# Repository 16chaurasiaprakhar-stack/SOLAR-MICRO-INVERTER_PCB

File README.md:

# HAR-SMI-500 — High-Altitude Resilient 500W Solar Micro-Inverter

A high-altitude, extreme-environment **500W solar micro-inverter architecture** designed for operation under subzero temperatures and reduced atmospheric pressure. The design combines a **GaN-based LLC DC-DC conversion stage**, isolated planar transformer, **SiC full-bridge grid inverter**, LCL filtering, deterministic C2000 control, and ESP32-S3-based edge telemetry.

The system is designed around a **28–50V DC PV input**, **400V DC-link**, and **230V AC / 50Hz grid output**, with a target peak efficiency of **97.2%**.

## Key Features

* **500W continuous power conversion**
* 28–50V DC photovoltaic input
* 400V regulated DC-link
* 230V AC, 50Hz single-phase output
* GaN full-bridge LLC converter
* 2:20 planar isolation transformer
* SiC full-bridge grid inverter
* LCL output filter
* TI **TMS320F28379D C2000** real-time power controller
* **ESP32-S3** edge-processing and telemetry controller
* Galvanically isolated SPI communication using **ISO7741-Q1**
* Incremental Conductance MPPT
* SOGI-PLL grid synchronization
* 20kHz proportional-resonant current control
* Hardware over-voltage and over-current trip protection
* PT100, BME280, SHT45 and solar-irradiance sensing
* SX1262-based LoRaWAN telemetry
* Autonomous cold-start pre-heating using a 25W PTC heater
* High-altitude PCB clearance and creepage design
* Designed for −40°C to +55°C operation

The complete architecture is divided into hierarchical functional blocks covering PV input protection, LLC conversion, isolation and rectification, DC-link storage, SiC inversion, LCL filtering, gate drivers, sensing, dual-MCU control, RF telemetry, auxiliary power, and mechanical interfaces.

## Control & Protection

The C2000 controller provides the deterministic power-conversion control loop, including MPPT, LLC frequency modulation, grid synchronization, PR current control, and hardware Trip-Zone protection. The ESP32-S3 is isolated from the power-control domain and handles environmental diagnostics, cold-start supervision, data logging, and wireless telemetry.

## High-Altitude Design

The architecture incorporates altitude-aware electrical insulation design with an enforced **≥4.5 mm clearance** and **≥6.0 mm creepage**, along with milled isolation slots, conformal coating, selective potting, and minimized high-dv/dt power loops.

## Cold-Start System  

At temperatures below −20°C, the system enters an autonomous pre-heating state before enabling normal inverter operation. A 25W PTC heater combined with controlled GaN switching provides approximately 38W of heating power, targeting a transition from −40°C to −10°C in approximately 11.58 minutes.

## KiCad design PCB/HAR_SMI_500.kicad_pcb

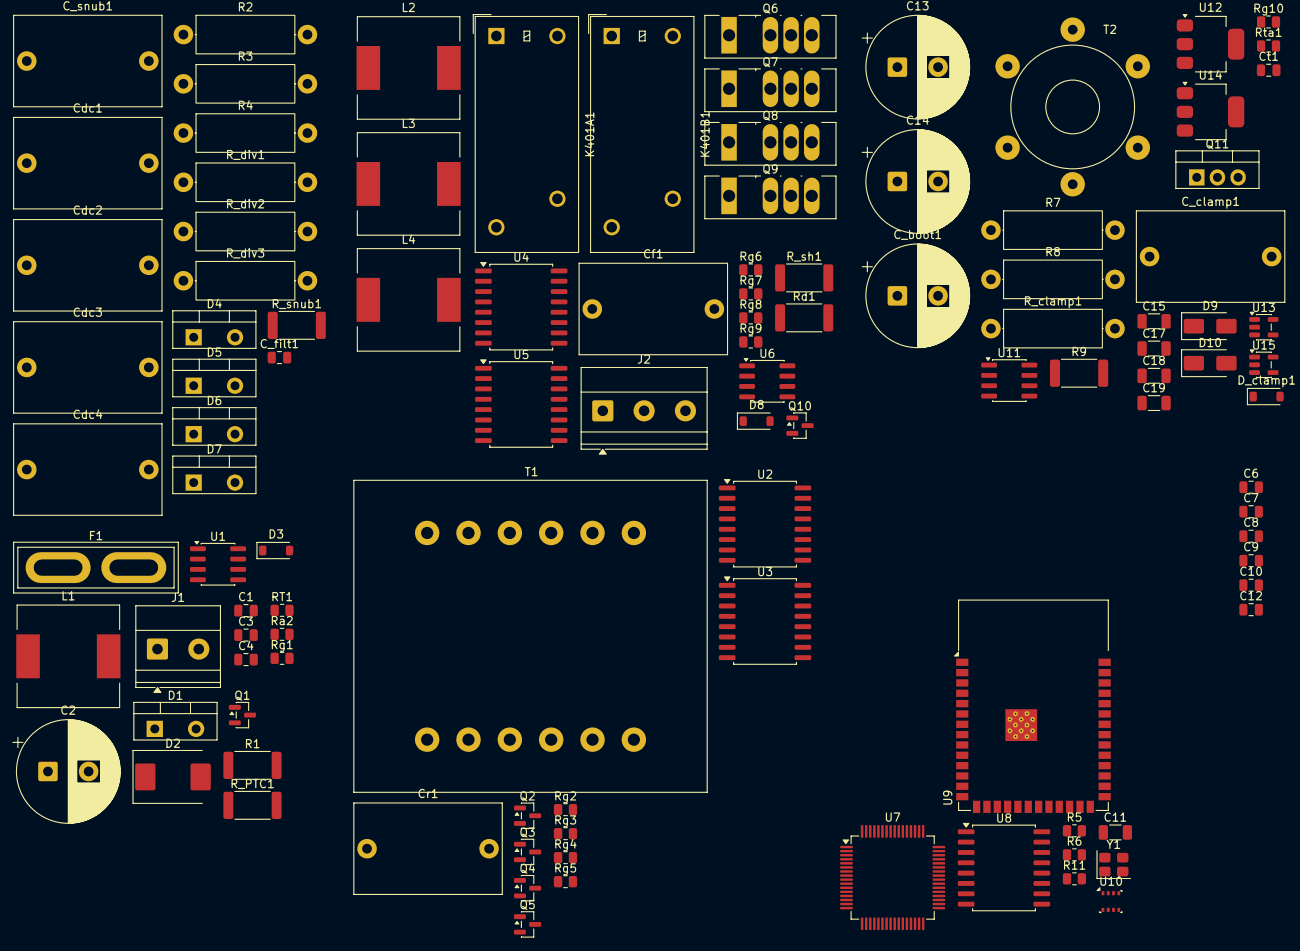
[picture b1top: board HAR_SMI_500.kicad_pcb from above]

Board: 2 copper layers, 108 parts (0 on the bottom side), 90 nets, no tracks yet.

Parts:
C1: 10uF 100V X7R MLCC; C_0805_2012Metric
C2: 470uF 100V Electrolytic; CP_Radial_D12.5mm_P5.00mm
C3: 100nF 50V Decouple; C_0805_2012Metric
C4: 100nF 50V RTD Filter; C_0805_2012Metric
C6, C8: 18pF 50V C0G; C_0805_2012Metric
C7: 2.2uF VDDC Decouple; C_0805_2012Metric
C9: 0.1uF 50V (Pri Vcc); C_0805_2012Metric
C10: 0.1uF 50V (Sec Vcc); C_0805_2012Metric
C11: 1uF EN Delay; C_1206_3216Metric
C12: 10uF 10V (ESP 3V3); C_0805_2012Metric
C13: 100uF 35V Low-ESR; CP_Radial_D12.5mm_P5.00mm
C14: 220uF 16V Low-ESR; CP_Radial_D12.5mm_P5.00mm
C15: 10uF 25V; C_1206_3216Metric
C17, C19: 10uF 10V; C_1206_3216Metric
C18: 10uF 16V; C_1206_3216Metric
C_boot1: 47uF 35V Low-ESR; CP_Radial_D12.5mm_P5.00mm
C_clamp1: 2.2nF 1kV; C_Rect_L18.0mm_W11.0mm_P15.00mm_FKS3_FKP3
C_filt1: 10nF 50V C0G ADC Filter; C_0805_2012Metric
C_snub1: 1nF 1kV Ceramic; C_Rect_L18.0mm_W11.0mm_P15.00mm_FKS3_FKP3
Cdc1, Cdc2, Cdc3, Cdc4: 47uF 450V Polypropylene; C_Rect_L18.0mm_W11.0mm_P15.00mm_FKS3_FKP3
Cf1: 4.7uF 305V AC; C_Rect_L18.0mm_W11.0mm_P15.00mm_FKS3_FKP3
Cr1: 660nF 100V Resonant Cap; C_Rect_L18.0mm_W11.0mm_P15.00mm_FKS3_FKP3
Ct1: 1nF C0G; C_0805_2012Metric
D1: V30100P Schottky (30A, 100V); TO-220-2_Vertical
D2: 5.0SMDJ58A TVS (58V); D_SMC
D3, D8: 1N4148 Clamp; D_SOD-123
D4, D5, D6, D7: C3D10060A SiC (600V 10A); TO-220-2_Vertical
D9: MBR1100 (100V 1A); D_SMA
D10: MBR160 (60V 1A); D_SMA
D_clamp1: UF4007 (Fast 1kV); D_SOD-123
F1: 20A Fast Blade Fuse; Fuse_Blade_ATO_directSolder
J1: PV Input Terminal Block; TerminalBlock_Phoenix_MKDS-1,5-2-5.08_1x02_P5.08mm_Horizont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
J2: 230V AC Grid; TerminalBlock_Phoenix_MKDS-1,5-3-5.08_1x03_P5.08mm_Horizont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
K401A1: Line Contactor (G2RL-1A); Relay_SPST_Omron_G2RL-1A
K401B1: Neut Contactor (G2RL-1A); Relay_SPST_Omron_G2RL-1A
L1: 0.8mH CM Choke (20A); L_12x12mm_H8mm
L2: 1.8 mH Line; L_12x12mm_H8mm
L3: 1.8 mH Neut; L_12x12mm_H8mm
L4: 0.6 mH Grid; L_12x12mm_H8mm
Q1: CSD18540Q5B (60V 100A); SOT-23
Q2, Q3, Q4, Q5: EPC2020 (60V GaN); SOT-23
Q6, Q7, Q8, Q9: C3M0075120K (SiC); TO-247-4_Vertical
Q10: 2N7002 Driver; SOT-23
Q11: STP10NK60Z (600V); TO-220-3_Vertical
R1: 2 mOhm 5W 0.1% Shunt; R_2512_6332Metric
R2, R3, R4: 150k 1W HV Bleeder; R_Axial_DIN0414_L11.9mm_D4.5mm_P15.24mm_Horizontal
R5: 10k Reset Pull-up; R_0805_2012Metric
R6: 10k EN Pull-up; R_0805_2012Metric
R7, R8: 100k 1W Trickle; R_Axial_DIN0414_L11.9mm_D4.5mm_P15.24mm_Horizontal
R9: 0.33R 2W Shunt; R_2512_6332Metric
R11: 10k SDO Pulldown; R_0805_2012Metric
RT1: PT1000 RTD Sensor; R_0805_2012Metric
R_PTC1: 25W Ceramic PTC Heater; R_2512_6332Metric
R_clamp1: 100k 2W; R_Axial_DIN0414_L11.9mm_D4.5mm_P15.24mm_Horizontal
R_div1, R_div2: 499k 0.1% HV Divider; R_Axial_DIN0414_L11.9mm_D4.5mm_P15.24mm_Horizontal
R_div3: 10k 0.1% Low-Side; R_Axial_DIN0414_L11.9mm_D4.5mm_P15.24mm_Horizontal
R_sh1: 5 mOhm 5W; R_2512_6332Metric
R_snub1: 22 Ohm 2W Flameproof; R_2512_6332Metric
Ra2: 1.00k 0.1% RTD Bias; R_0805_2012Metric
Rd1: 3.3R 5W Damp; R_2512_6332Metric
Rg1: 10 Ohm Gate; R_0805_2012Metric
Rg2, Rg3, Rg4, Rg5: 4.7 Ohm GaN; R_0805_2012Metric
Rg6, Rg7, Rg8, Rg9: 10 Ohm SiC; R_0805_2012Metric
Rg10: 22 Ohm; R_0805_2012Metric
Rta1: 47k 1%; R_0805_2012Metric
T1: Planar Transformer 1:12; Transformer_37x44
T2: Flyback Transformer (1P/2S); Transformer_Toroid_Tapped_Horizontal_D14.0mm_Amidon-T50
U1: INA240A1D (Gain=20); SOIC-8_3.9x4.9mm_P1.27mm
U2: UCC21520DW (GaN Leg A); SOIC-16W_7.5x10.3mm_P1.27mm
U3: UCC21520DW (GaN Leg B); SOIC-16W_7.5x10.3mm_P1.27mm
U4: UCC21520DW (SiC Leg 1); SOIC-16W_7.5x10.3mm_P1.27mm
U5: UCC21520DW (SiC Leg 2); SOIC-16W_7.5x10.3mm_P1.27mm
U6: INA240A1D (Grid Current); SOIC-8_3.9x4.9mm_P1.27mm
U7: TMS320F280049C (100MHz DSP); LQFP-64_10x10mm_P0.5mm
U8: ISO7762DW (5kVrms Barrier); SOIC-16W_7.5x10.3mm_P1.27mm
U9: ESP32-S3-WROOM-1 (IoT); ESP32-S3-WROOM-1
U10: BME280 Env Sensor; Bosch_LGA-8_2.5x2.5mm_P0.65mm_ClockwisePinNumbering
U11: UCC3800 (BiCMOS Flyback); SOIC-8_3.9x4.9mm_P1.27mm
U12: LM7815 (+15V SiC Rail); SOT-223-3_TabPin2
U13: TLV75533 (+3V3_PRI DSP); SOT-23-5
U14: LM7805 (+5V_SEC Pre-Reg); SOT-223-3_TabPin2
U15: TLV75533 (+3V3_SEC IoT); SOT-23-5
Y1: 20MHz C0G Crystal; Crystal_SMD_3225-4Pin_3.2x2.5mm

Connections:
400V_DC_POS: Cdc1.1, Cdc2.1, Cdc3.1, Cdc4.1, D4.1 (K), D6.1 (K), Q6.2 (D), Q8.2 (D), R2.1, R3.1, R4.1, R_div1.1
+3V3_PRI: C9.1, C17.1, R5.1, Ra2.1, U7.2 (VDDA), U7.11 (VDD), U7.26 (VDD), U7.42 (VDD), U7.54 (VDD), U8.1 (Vcc1), U13.5 (OUT)
+3V3_SEC: C10.1, C12.1, C19.1, R6.1, U8.16 (Vcc2), U9.2 (3V3), U10.2 (CSB), U10.6 (VDDIO), U10.8 (VDD), U15.5 (OUT)
+5V_PRI: C1.2, C2.2, C3.1, C3.2, C4.2, C6.2, C7.2, C8.2, C9.2, C13.2, C14.1, C14.2, C15.2, C17.2, C18.2, C19.2, C_boot1.2, Ct1.2, D2.2 (A2), D10.1 (K), J1.2, Q1.3 (S), Q3.3 (S), Q5.3 (S), R9.2, RT1.2, T2.4 (SB), T2.6 (SD), U1.2 (GND), U1.3 (REF2), U1.4 (GND), U1.6 (V+), U1.7 (REF1), U2.3 (VCCI), U2.4 (GND), U2.5 (DIS), U2.6 (DT), U2.8 (VCCI), U2.9 (VSSB), U2.11 (VDDB), U2.16 (VDDA), U3.3 (VCCI), U3.4 (GND), U3.5 (DIS), U3.6 (DT), U3.8 (VCCI), U3.9 (VSSB), U3.11 (VDDB), U3.16 (VDDA), U7.3 (GNDA), U7.12 (GND), U7.27 (GND), U7.39 (GND), U7.55 (GND), U8.8 (GND1), U11.5 (GND), U12.2 (GND), U13.1 (IN), U13.2 (GND), U13.3 (EN), U14.2 (GND), U15.2 (GND)
+5V_SEC: C18.1, U4.3 (VCCI), U4.8 (VCCI), U5.3 (VCCI), U5.8 (VCCI), U6.6 (V+), U14.3 (VO), U15.1 (IN), U15.3 (EN)
+15V_SEC: C15.1, D8.1 (K), K401A1.A1, K401B1.A1, U4.11 (VDDB), U4.16 (VDDA), U5.11 (VDDB), U5.16 (VDDA), U12.3 (VO), U14.1 (VI)
/Aux Multi-Rail Supply/FLYBACK_SW: C_clamp1.2, D_clamp1.2 (A), Q11.2 (D), R_clamp1.2
/Aux Multi-Rail Supply/T2_SEC1_AC: D10.2 (A), T2.3 (SA)
/Aux Multi-Rail Supply/T2_SEC2_AC: D9.2 (A), T2.5 (SC)
/Aux Multi-Rail Supply/TRICKLE_MID: R7.2, R8.1
/Aux Multi-Rail Supply/UCC_CS: Q11.3 (S), R9.1, U11.3 (CS)
/Aux Multi-Rail Supply/UCC_FB: U11.1 (COMP), U11.2 (FB)
/Aux Multi-Rail Supply/UCC_GATE: Q11.1 (G), Rg10.2
/Aux Multi-Rail Supply/UCC_OUT: Rg10.1, U11.6 (OUT)
/Aux Multi-Rail Supply/UCC_RC: Ct1.1, Rta1.2, U11.4 (RC)
/Aux Multi-Rail Supply/UCC_REF: Rta1.1, U11.8 (REF)
/Dual MCU & Telemetry/BME_SDO: R11.1, U10.5 (SDO)
/Dual MCU & Telemetry/DSP_RELAY_EN: U7.21 (SSI0RX/PA4), U8.5 (IND)
/Dual MCU & Telemetry/DSP_RESET: R5.2, U7.38 (~RST)
/Dual MCU & Telemetry/DSP_SPI_CLK: U7.19 (SSI0CLK/PA2), U8.2 (INA)
/Dual MCU & Telemetry/DSP_SPI_CS: U7.20 (SSI0FSS/PA3), U8.4 (INC)
/Dual MCU & Telemetry/DSP_SPI_MISO: U7.1 (I2C5SCL/SSI2RX/T0CCP0/PB6), U8.6 (OUTE)
/Dual MCU & Telemetry/DSP_SPI_MOSI: U7.22 (SSI0TX/PA5), U8.3 (INB)
/Dual MCU & Telemetry/ESP_EN: C11.2, R6.2, U9.3 (EN)
/Dual MCU & Telemetry/I2C_SCL_SEC: U9.5 (IO5), U10.4 (SCK)
/Dual MCU & Telemetry/I2C_SDA_SEC: U9.4 (IO4), U10.3 (SDI)
/Dual MCU & Telemetry/OSC_IN: C6.1, U7.40 (OSC0), Y1.1
/Dual MCU & Telemetry/OSC_OUT: C8.1, U7.41 (OSC1), Y1.2
/Dual MCU & Telemetry/SEC_SPI_CLK: U8.15 (OUTA), U9.18 (IO10)
/Dual MCU & Telemetry/SEC_SPI_CS: U8.13 (OUTC), U9.12 (IO8)
/Dual MCU & Telemetry/SEC_SPI_MISO: U8.11 (INE), U9.17 (IO9)
/Dual MCU & Telemetry/SEC_SPI_MOSI: U8.14 (OUTB), U9.19 (IO11)
/Dual MCU & Telemetry/VDDC: C7.1, U7.25 (VDDC), U7.56 (VDDC)
/LLC Converter & GaN/LLC_DRV_H1: Rg4.1, U2.15 (OUTA)
/LLC Converter & GaN/LLC_DRV_H2: Rg2.1, U3.15 (OUTA)
/LLC Converter & GaN/LLC_DRV_L1: Rg5.1, U2.10 (OUTB)
/LLC Converter & GaN/LLC_DRV_L2: Rg3.1, U3.10 (OUTB)
/LLC Converter & GaN/LLC_GATE_H1: Q2.1 (G), Rg4.2
/LLC Converter & GaN/LLC_GATE_H2: Q4.1 (G), Rg2.2
/LLC Converter & GaN/LLC_GATE_L1: Q3.1 (G), Rg5.2
/LLC Converter & GaN/LLC_GATE_L2: Q5.1 (G), Rg3.2
/LLC Converter & GaN/LLC_MID_TANK: Cr1.2, T1.1 (AA)
/LLC Converter & GaN/SW_A: Cr1.1, Q2.3 (S), Q3.2 (D), U2.14 (VSSA)
/LLC Converter & GaN/SW_B: Q4.3 (S), Q5.2 (D), T1.2 (AB), U3.14 (VSSA)
/PV Input & Protection/HEATER_SW_DRAIN: D3.2 (A), Q1.2 (D), R_PTC1.2
/PV Input & Protection/PV_FILT_POS: C1.1, C2.1, L1.2, R1.1, U1.8 (+)
/PV Input & Protection/PV_IN_FUSE: D1.2 (A), F1.2
/PV Input & Protection/PV_IN_PROT: D1.1 (K), D2.1 (A1), L1.1
/PV Input & Protection/PV_IN_RAW: F1.1, J1.1
/SiC Inverter & Filter/GRID_LINE: J2.1, K401A1.14
/SiC Inverter & Filter/GRID_NEUT: J2.2, K401B1.14
/SiC Inverter & Filter/INV_SW1: L2.1, Q6.3 (S), Q7.2 (D), U4.14 (VSSA)
/SiC Inverter & Filter/INV_SW2: L3.1, Q8.3 (S), Q9.2 (D), U5.14 (VSSA)
/SiC Inverter & Filter/L4_OUT: L4.2, R_sh1.1, U6.8 (+)
/SiC Inverter & Filter/LCL_DAMP: Cf1.2, Rd1.1
/SiC Inverter & Filter/LCL_LINE_MID: Cf1.1, L2.2, L4.1
/SiC Inverter & Filter/LCL_NEUT_MID: K401B1.13, L3.2, Rd1.2
/SiC Inverter & Filter/LINE_PRE_RELAY: K401A1.13, R_sh1.2, U6.1 (-)
/SiC Inverter & Filter/RELAY_COIL_LO: D8.2 (A), K401A1.A2, K401B1.A2, Q10.2 (D)
/SiC Inverter & Filter/SIC_DRV_H1: Rg6.1, U4.15 (OUTA)
/SiC Inverter & Filter/SIC_DRV_H2: Rg8.1, U5.15 (OUTA)
/SiC Inverter & Filter/SIC_DRV_L1: Rg7.1, U4.10 (OUTB)
/SiC Inverter & Filter/SIC_DRV_L2: Rg9.1, U5.10 (OUTB)
/SiC Inverter & Filter/SIC_GATE_H1: Q6.1 (G), Rg6.2
/SiC Inverter & Filter/SIC_GATE_H2: Q8.1 (G), Rg8.2
/SiC Inverter & Filter/SIC_GATE_L1: Q7.1 (G), Rg7.2
/SiC Inverter & Filter/SIC_GATE_L2: Q9.1 (G), Rg9.2
GRID_CURRENT_ADC: U6.5, U7.62 (AIN6/I2C3SDA/SSI1FSS/SSI3FSS/WT2CCP1/PD1)
HEATER_PWM_EN: Rg1.1, U7.18 (U0TX/PA1)
ISENSE_PV: U1.5, U7.64 (AIN4/SSI1TX/SSI3TX/WT3CCP1/PD3)
unnamed: C_snub1.2, R_snub1.1
unnamed: C13.1, D9.1 (K), U12.1 (VI)
unnamed: Q1.1 (G), Rg1.2
unnamed: R_div1.2, R_div2.1
unnamed: C_boot1.1, R8.2, U11.7 (VCC)
PV_BUS_POS: C_clamp1.1, D3.1 (K), D_clamp1.1 (K), Q2.2 (D), Q4.2 (D), R1.2, R7.1, R_PTC1.1, R_clamp1.1, T2.1 (AA), T2.2 (AB), U1.1 (-)
PWM_H1: U2.1 (INA), U7.14 (C0+/U3RX/WT1CCP0/PC6)
PWM_H2: U3.1 (INA), U7.16 (C1-/U1RTS/U1RX/U4RX/WT0CCP0/PC4)
PWM_L1: U2.2 (INB), U7.15 (C1+/U1CTS/U1TX/U4TX/WT0CCP1/PC5)
PWM_L2: U3.2 (INB), U7.17 (U0RX/PA0)
RELAY_GRID_EN: Q10.1 (G), U8.12 (OUTD)
SEC_GND: C10.2, C11.1, C12.2, C_filt1.2, Cdc1.2, Cdc2.2, Cdc3.2, Cdc4.2, D5.2 (A), D7.2 (A), Q7.3 (S), Q9.3 (S), Q10.3 (S), R2.2, R3.2, R4.2, R11.2, R_div3.2, U4.4 (GND), U4.5 (DIS), U4.6 (DT), U4.9 (VSSB), U5.4 (GND), U5.5 (DIS), U5.6 (DT), U5.9 (VSSB), U6.2 (GND), U6.3 (REF2), U6.4 (GND), U6.7 (REF1), U8.9 (GND2), U8.10 (INF), U9.1 (GND), U9.40 (GND), U9.41 (GND), U10.1 (GND), U10.7 (GND)
SIC_PWM_H1: U4.1 (INA), U7.57 (AIN11/CAN0TX/SSI2FSS/T1CCP1/PB5)
SIC_PWM_H2: U5.1 (INA), U7.59 (PE4/AIN9/U5RX/I2C2SCL/CAN0RX)
SIC_PWM_L1: U4.2 (INB), U7.58 (AIN10/CAN0RX/SSI2CLK/T1CCP0/PB4)
SIC_PWM_L2: U5.2 (INB), U7.60 (PE5/AIN8/U5TX/I2C2SDA/CAN0TX)
T1_SEC_N: D6.2 (A), D7.1 (K), R_snub1.2, T1.3 (SA)
T1_SEC_P: C_snub1.1, D4.2 (A), D5.1 (K), T1.4 (SB)
TEMP_SENSE_PT1000: C4.1, RT1.1, Ra2.2, U7.61 (AIN7/I2C3SCL/SSI1CLK/SSI3CLK/WT2CCP0/PD0)
VDC_SENSE_ADC: C_filt1.1, R_div2.2, R_div3.1, U7.63 (AIN5/SSI1RX/SSI3RX/WT3CCP0/PD2)
